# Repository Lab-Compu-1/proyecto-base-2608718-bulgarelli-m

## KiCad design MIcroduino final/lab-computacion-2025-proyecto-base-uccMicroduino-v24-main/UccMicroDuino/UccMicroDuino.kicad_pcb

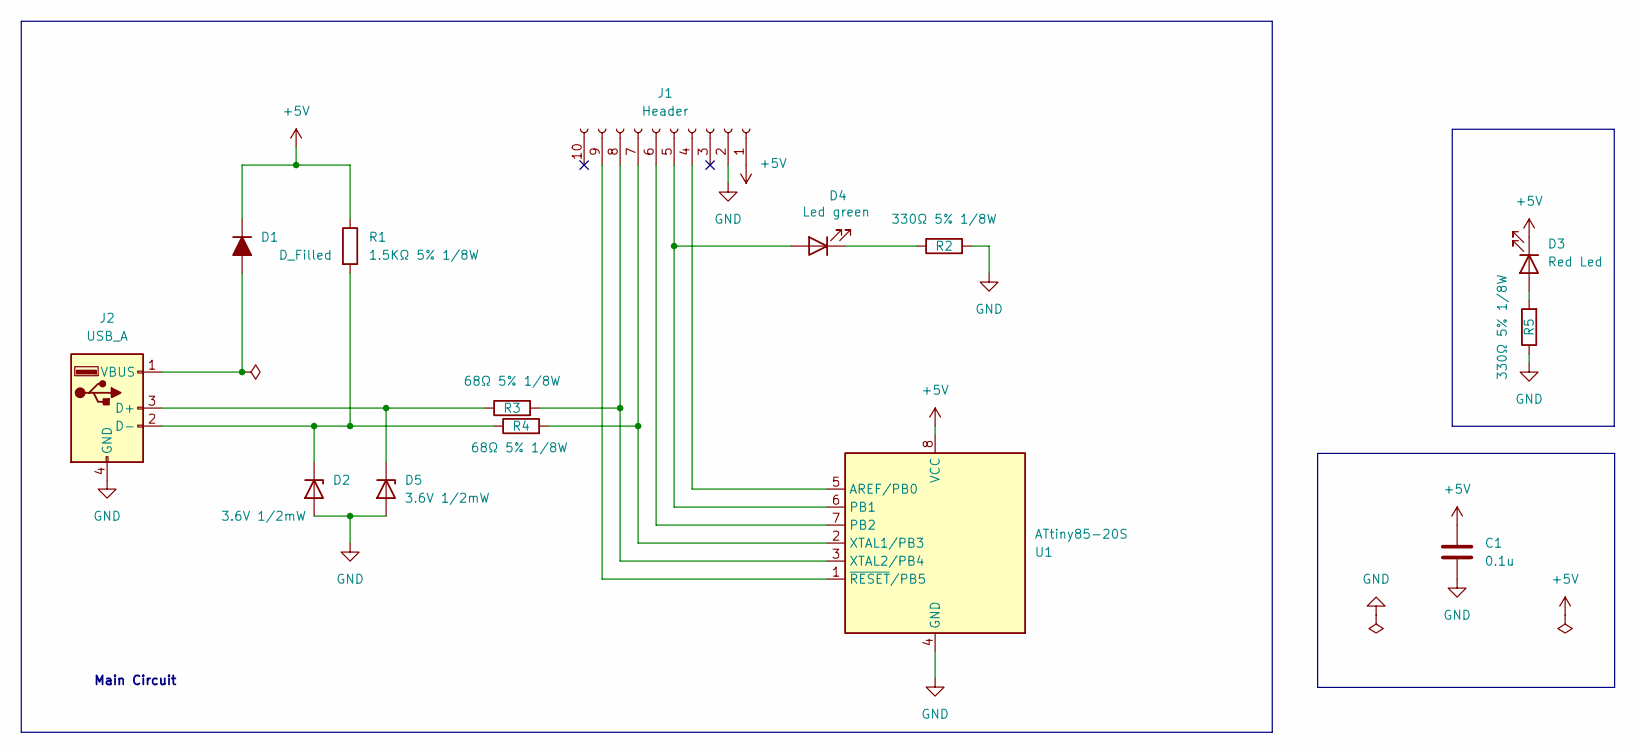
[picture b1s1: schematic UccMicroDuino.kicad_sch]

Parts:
C1: 0.1u; C_0805_2012Metric_Pad1.18x1.45mm_HandSolder
D1: D_Filled; D_MiniMELF
D2, D5: 3.6V 1/2mW; D_SOD-123
D3: Red Led; ledSMD
D4: Led green; ledSMD
J1: Header; PinHeader_1x10_P2.54mm_Vertical
J2: USB_A; USB_A_UCC
R1: 1.5KΩ 5% 1/8W; R_0805_2012Metric_Pad1.20x1.40mm_HandSolder
R2, R5: 330Ω 5% 1/8W; R_0805_2012Metric_Pad1.20x1.40mm_HandSolder
R3, R4: 68Ω 5% 1/8W; R_0805_2012Metric_Pad1.20x1.40mm_HandSolder
U1: ATtiny85-20S; SOIC-8W_5.3x5.3mm_P1.27mm

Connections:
+5V: C1.1, D1.1 (K), D3.1 (K), J1.1, R1.1, U1.8 (VCC)
GND: C1.2, D2.2 (A), D5.2 (A), J1.2, J2.4 (GND), R2.2, R5.1, U1.4 (GND)
unnamed: D1.2 (A), J2.1 (VBUS)
unnamed: D2.1 (K), J2.2 (D-), R1.2, R4.1
unnamed: D3.2 (A), R5.2
unnamed: D4.2 (A), J1.5, U1.6 (PB1)
unnamed: D4.1 (K), R2.1
unnamed: D5.1 (K), J2.3 (D+), R3.1
unnamed: J1.4, U1.5 (AREF/PB0)
unnamed: J1.6, U1.7 (PB2)
unnamed: J1.7, R4.2, U1.2 (XTAL1/PB3)
unnamed: J1.8, R3.2, U1.3 (XTAL2/PB4)
unnamed: J1.9, U1.1 (~RESET/PB5)

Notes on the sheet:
Main Circuit

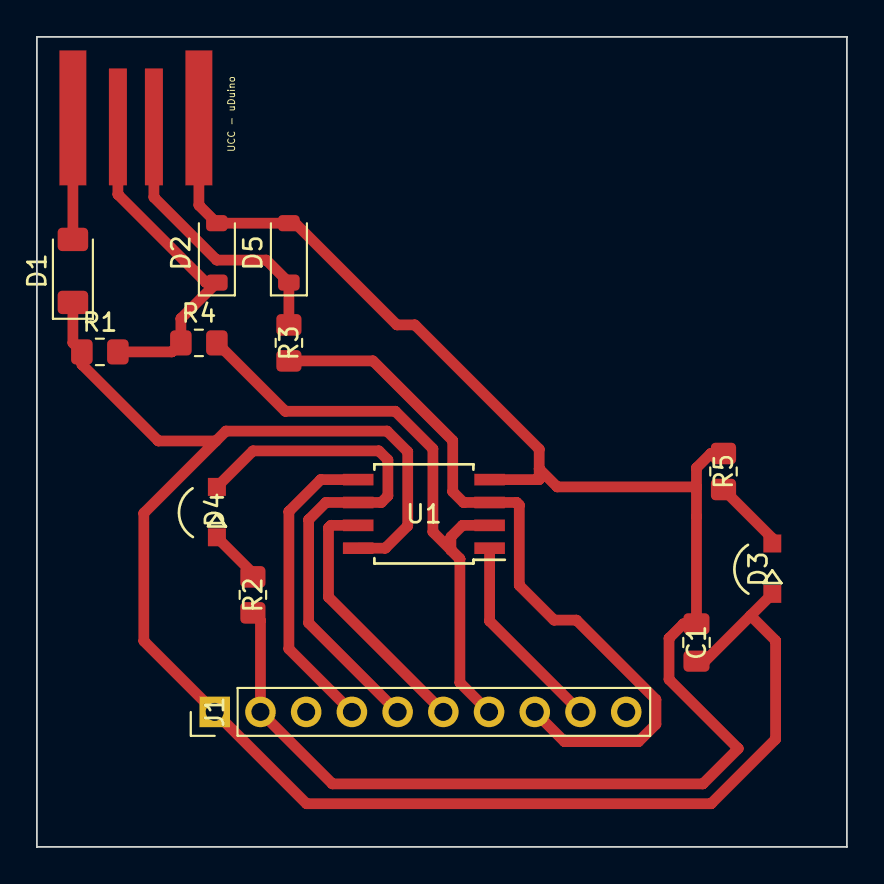
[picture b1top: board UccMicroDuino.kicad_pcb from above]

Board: 2 copper layers, 45.0 x 45.0 mm, 14 parts (0 on the bottom side), 13 nets.

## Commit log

2026-03-31 GitHub Classroom Feedback
2026-03-31 Setting up GitHub Classroom Feedback
2026-05-18 2608718-mi primer versionado en gitBash
